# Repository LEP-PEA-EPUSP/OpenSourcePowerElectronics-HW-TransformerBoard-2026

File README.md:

# OpenSourcePowerElectronics-HW-TransformerBoard-2026

This repository contains the manuals, schematics and layout needed to build and test the transformer board.

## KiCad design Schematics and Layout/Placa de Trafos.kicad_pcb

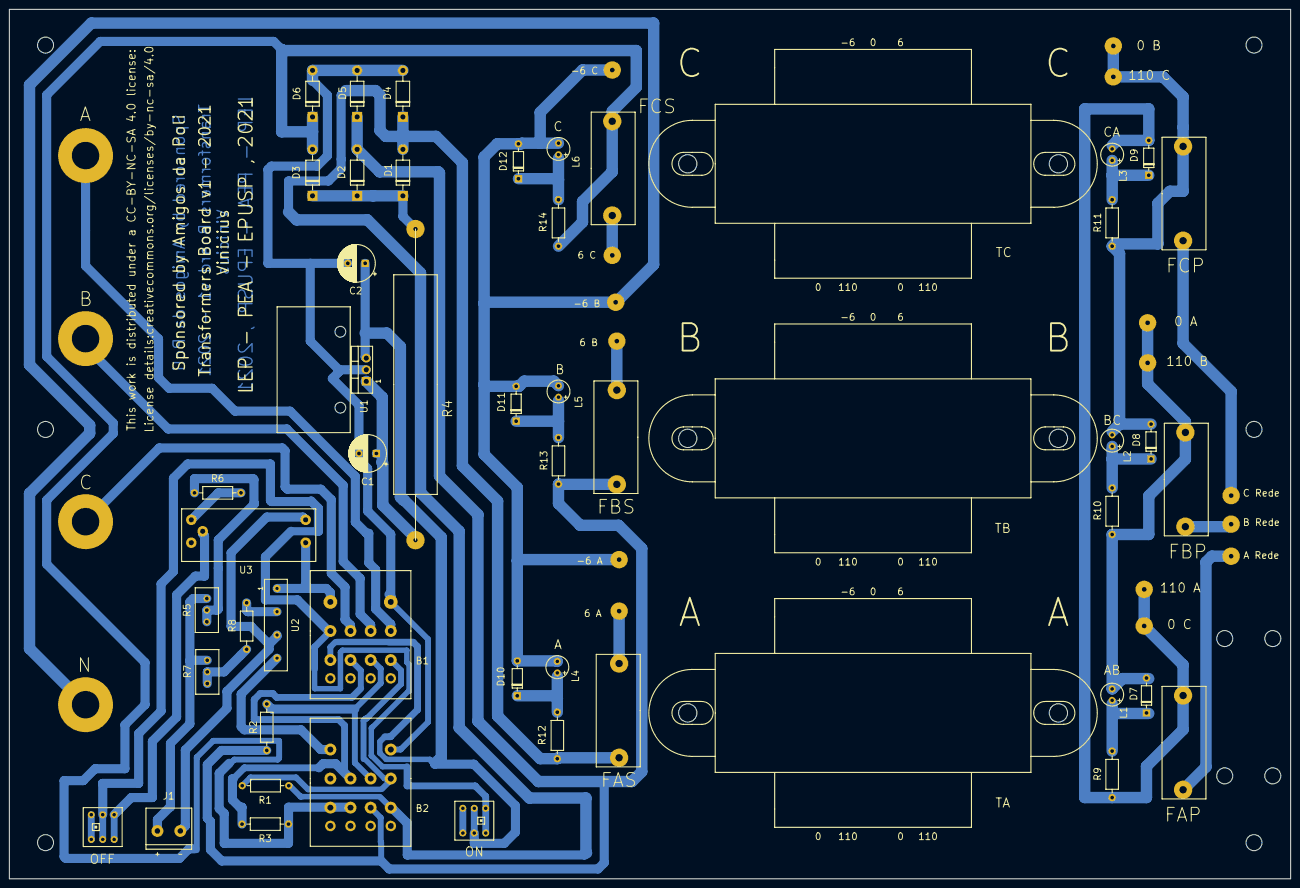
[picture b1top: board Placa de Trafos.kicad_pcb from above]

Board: 2 copper layers, 280.0 x 190.0 mm, 80 parts (0 on the bottom side), 39 nets.

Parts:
0_A1, 0_B1, 0_C1, 6_A1, 6_B1, 6_C1, 110_A1, 110_B1, 110_C1: Conn_01x01_Female; cabo_PP
-6_A1, -6_B1, -6_C1: Conn_01x01_Female; cabo_PP
A1: Conn_01x01_Female; Borne
A_rede1: Conn_01x01_Female; cabo_PP
B1, B2: rele_4C; Soquete_Rele_PT570012
B3: Conn_01x01_Female; Borne
B_rede1: Conn_01x01_Female; cabo_PP
C1: 100u/63V; CP_Radial_D8.0mm_P3.80mm
C2: 100u/25V; CP_Radial_D8.0mm_P3.80mm
C3: Conn_01x01_Female; Borne
C_rede1: Conn_01x01_Female; cabo_PP
D1, D2, D3, D4, D5, D6: 1N4001; D_DO-41_SOD81_P10.16mm_Horizontal
D7, D8, D9, D10, D11, D12: 1N4148; D_DO-35_SOD27_P7.62mm_Horizontal
FAP1: Fuse; Porta_Fuse
FAS1: Fuse; Porta_Fuse
FBP1: Fuse; Porta_Fuse
FBS1: Fuse; Porta_Fuse
FCP1: Fuse; Porta_Fuse
FCS1: Fuse; Porta_Fuse
Furo1, Furo2, Furo3, Furo4, Furo5, Furo6, Furo7, Furo8, Furo9, Furo10: Conn_01x01_Female; Furo-pé
J1: Conn_01x02_Female; Conector_parafuso
L1, L2, L3, L4, L5, L6: LED; LED_placa
N1: Conn_01x01_Female; Borne
OFF1: SW_Push_Open; Botao_OFF
ON1: SW_Push; Botao_ON
R1: 33ohms/2w; R_Axial_DIN0207_L6.3mm_D2.5mm_P10.16mm_Horizontal
R2, R3: R; R_Axial_DIN0207_L6.3mm_D2.5mm_P10.16mm_Horizontal
R4: 47ohms/10w; Resistor_10W_porcelana
R5, R7: 2k trimpot; Potentiometer_Bourns_3296W_Vertical
R6: 7k5/1W; R_Axial_DIN0207_L6.3mm_D2.5mm_P10.16mm_Horizontal
R8: 3k3/1W; R_Axial_DIN0207_L6.3mm_D2.5mm_P10.16mm_Horizontal
R9, R10, R11: 100k/2w; R_Axial_DIN0207_L6.3mm_D2.5mm_P10.16mm_Horizontal
R12, R13, R14: 3k3-1/4w; R_Axial_DIN0207_L6.3mm_D2.5mm_P10.16mm_Horizontal
TA1: Transformer_SP_2S; Trafo
TB1: Transformer_SP_2S; Trafo
TC1: Transformer_SP_2S; Trafo
U1: LM7812_TO220; Dissipador
U2: rele_PC; relay_SH1NAC2
U3: rele_ST; relay_RU617112

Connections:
unnamed: 0_A1.1, 110_B1.1, D7.2, FBP1.2, L1.1, R10.1
unnamed: 0_B1.1, 110_C1.1, D8.2, FCP1.2, L2.1, R11.1
unnamed: 0_C1.1, 110_A1.1, D9.2, FAP1.2, L3.1, R9.1
unnamed: 6_A1.1, FAS1.1
unnamed: 6_B1.1, FBS1.1
unnamed: 6_C1.1, FCS1.1
unnamed: -6_A1.1, -6_B1.1, -6_C1.1, D10.2, D11.2, D12.2, L4.1, L5.1, L6.1, N1.1
unnamed: A1.1, B1.41
unnamed: A_rede1.1, FAP1.1
unnamed: B1.11, OFF1.2, ON1.1
unnamed: B1.14, C2.1, ON1.2, U1.3
unnamed: B1.21, C3.1
unnamed: B1.24, B2.21, R3.2
unnamed: B1.31, B3.1
unnamed: B1.34, B2.31, R2.2
unnamed: B1.44, B2.41, R1.2
unnamed: B1.A1, U2.1, U3.3
unnamed: B1.A2, B2.A2, C1.2, C2.2, D4.2, D5.2, D6.2, U1.2
unnamed: B2.14, B2.24, D3.2, D6.1, FCS1.2, R3.1, R14.1
unnamed: B2.34, D2.2, D5.1, FBS1.2, R2.1, R13.1
unnamed: B2.44, D1.2, D4.1, FAS1.2, R1.1, R12.1
unnamed: B2.A1, U2.7
unnamed: B_rede1.1, FBP1.1
unnamed: C1.1, R4.2, U1.1
unnamed: C_rede1.1, FCP1.1
unnamed: D1.1, D2.1, D3.1, R4.1
unnamed: D7.1, L1.2, R9.2
unnamed: D8.1, L2.2, R10.2
unnamed: D9.1, L3.2, R11.2
unnamed: D10.1, L4.2, R12.2
unnamed: D11.1, L5.2, R13.2
unnamed: D12.1, L6.2, R14.2
unnamed: J1.1, R5.1, R7.1
unnamed: J1.2, U2.5, U3.1
unnamed: OFF1.1, U3.9
unnamed: R5.2, R5.3, R6.1
unnamed: R6.2, U3.2
unnamed: R7.2, R7.3, R8.1
unnamed: R8.2, U2.3

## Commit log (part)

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2026-06-19 Upload files
2026-06-19 Add photo

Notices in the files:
Schematics and Layout/Placa de Trafos.kicad_pcb:
License details:creativecommons.org/licenses/by-nc-sa/4.0
This work is distributed under a CC-BY-NC-SA 4.0 license:
